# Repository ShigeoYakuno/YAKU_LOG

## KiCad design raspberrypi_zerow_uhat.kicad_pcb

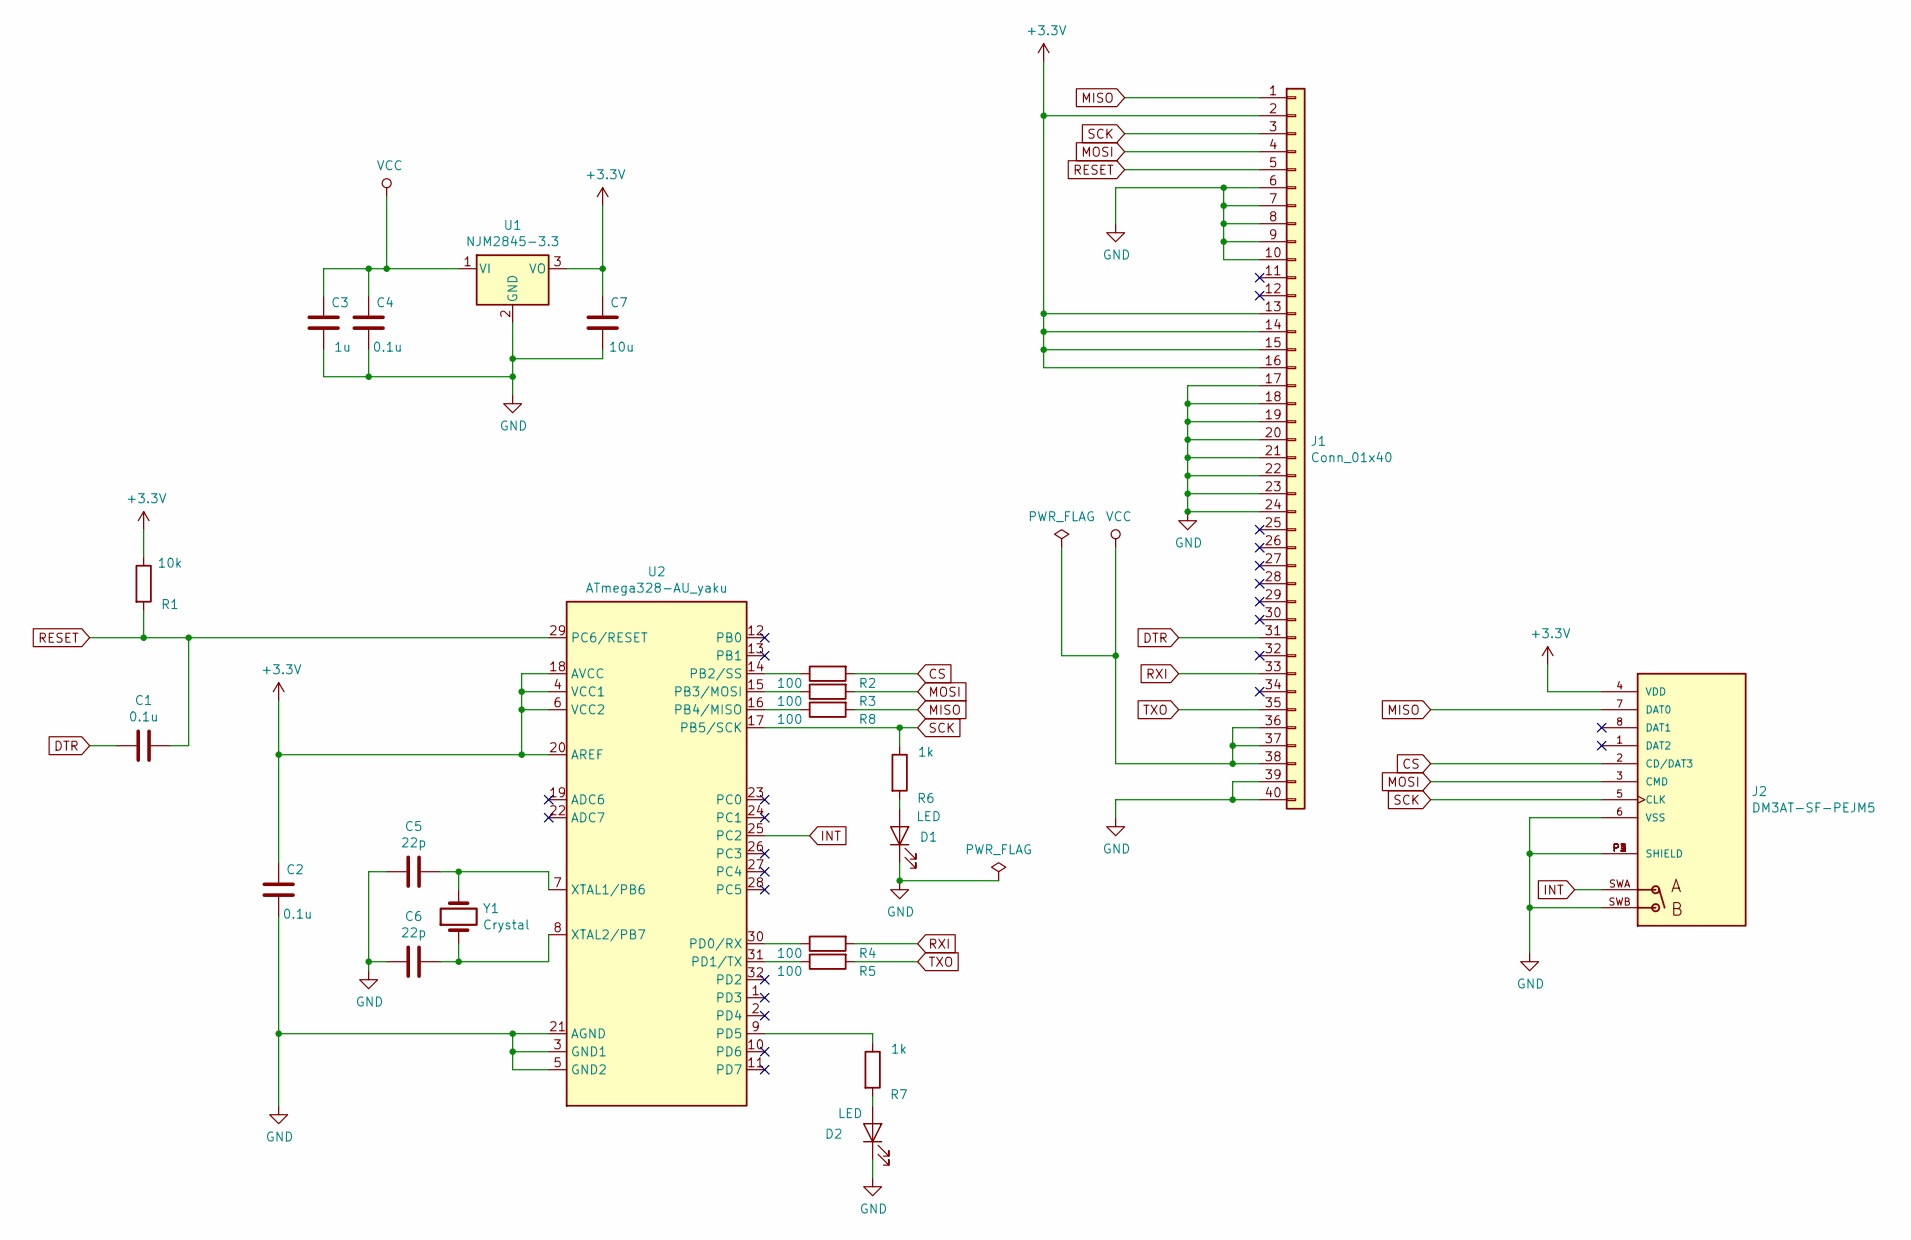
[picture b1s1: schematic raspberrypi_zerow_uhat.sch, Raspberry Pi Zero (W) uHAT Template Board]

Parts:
C1, C2, C4: 0.1u; C_0805_2012Metric_Pad1.18x1.45mm_HandSolder
C3: 1u; C_0805_2012Metric_Pad1.18x1.45mm_HandSolder
C5, C6: 22p; C_0603_1608Metric_Pad1.08x0.95mm_HandSolder
C7: 10u; C_0805_2012Metric_Pad1.18x1.45mm_HandSolder
D1, D2: LED; LED_0603_1608Metric
J1: Conn_01x40; PinHeader_2x20_P2.54mm_Vertical
J2: DM3AT-SF-PEJM5; HRS_DM3AT-SF-PEJM5
R1: 10k; R_0603_1608Metric_Pad0.98x0.95mm_HandSolder
R2, R3, R4, R5, R8: 100; R_0603_1608Metric_Pad0.98x0.95mm_HandSolder
R6, R7: 1k; R_0603_1608Metric_Pad0.98x0.95mm_HandSolder
U1: NJM2845-3.3; TO-252-2_Rectifier
U2: ATmega328-AU_yaku; TQFP-32_7x7mm
Y1: Crystal; XTAL1170X500X450

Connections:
+3V3: C2.2, C7.2, J1.2, J1.13, J1.14, J1.15, J1.16, J2.4 (VDD), R1.1, U1.3 (VO), U2.4 (VCC1), U2.6 (VCC2), U2.18 (AVCC), U2.20 (AREF)
CS: J2.2 (CD/DAT3), R2.2
DTR: C1.1, J1.31
GND: C2.1, C3.1, C4.1, C5.1, C6.1, C7.1, D1.1 (K), D2.1 (K), J1.6, J1.7, J1.8, J1.9, J1.10, J1.17, J1.18, J1.19, J1.20, J1.21, J1.22, J1.23, J1.24, J1.39, J1.40, J2.6 (VSS), J2.P1 (SHIELD), J2.P2 (SHIELD), J2.P3 (SHIELD), J2.P4 (SHIELD), J2.SWB, U1.2 (GND), U2.3 (GND1), U2.5 (GND2), U2.21 (AGND)
INT: J2.SWA, U2.25 (PC2)
MISO: J1.1, J2.7 (DAT0), R8.2
MOSI: J1.4, J2.3 (CMD), R3.2
unnamed: C5.2, U2.7 (XTAL1/PB6), Y1.2
unnamed: C6.2, U2.8 (XTAL2/PB7), Y1.1
unnamed: D1.2 (A), R6.2
unnamed: D2.2 (A), R7.2
unnamed: R2.1, U2.14 (PB2/SS)
unnamed: R3.1, U2.15 (PB3/MOSI)
unnamed: R4.1, U2.30 (PD0/RX)
unnamed: R5.1, U2.31 (PD1/TX)
unnamed: R7.1, U2.9 (PD5)
unnamed: R8.1, U2.16 (PB4/MISO)
RESET: C1.2, J1.5, R1.2, U2.29 (PC6/RESET)
RXI: J1.33, R4.2
SCK: J1.3, J2.5 (CLK), R6.1, U2.17 (PB5/SCK)
TXO: J1.35, R5.2
VCC: C3.2, C4.2, J1.36, J1.37, J1.38, U1.1 (VI)

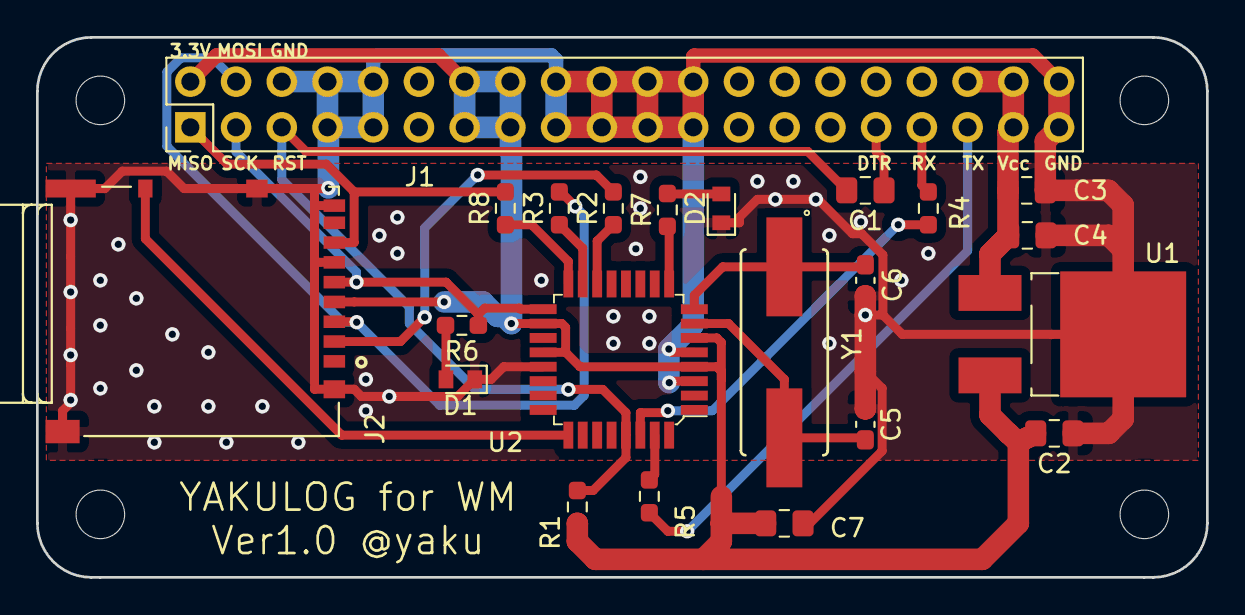
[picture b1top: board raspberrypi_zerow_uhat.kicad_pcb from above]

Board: 2 copper layers, 65.0 x 30.0 mm, 26 parts (0 on the bottom side), 22 nets.

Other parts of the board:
H1, H2, H3, H4: MountingHole; MountingHole_2.7mm_M2.5_uHAT_RPi

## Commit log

2023-12-18 ver1.0

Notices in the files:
raspberrypi_zerow_uhat.kicad_pcb:
This PCB design is licensed under MIT Open Source License.
raspberrypi_zerow_uhat.sch:
This Schematic is licensed under MIT Open Source License.
